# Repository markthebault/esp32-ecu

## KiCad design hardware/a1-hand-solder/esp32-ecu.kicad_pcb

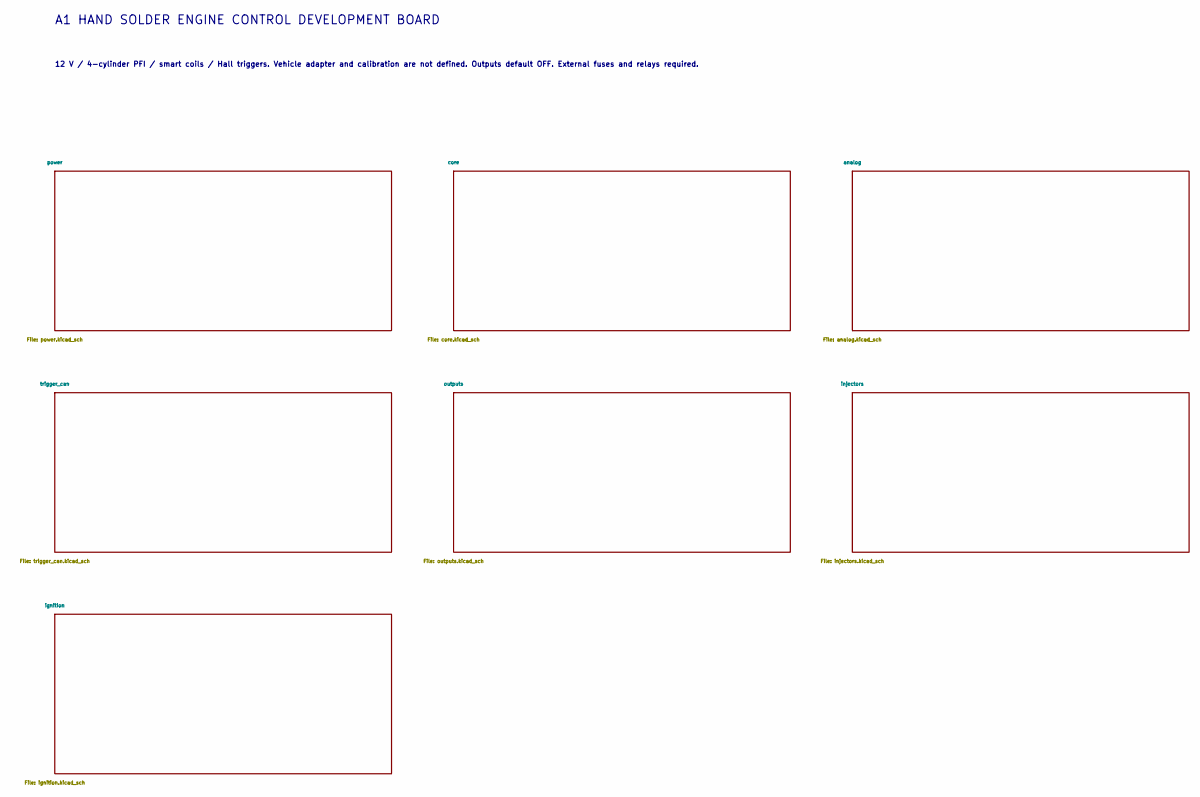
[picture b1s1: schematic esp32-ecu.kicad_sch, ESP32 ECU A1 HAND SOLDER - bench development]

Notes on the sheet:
A1 HAND SOLDER ENGINE CONTROL DEVELOPMENT BOARD
12 V / 4-cylinder PFI / smart coils / Hall triggers. Vehicle adapter and calibration are not defined. Outputs default OFF. External fuses and relays required.

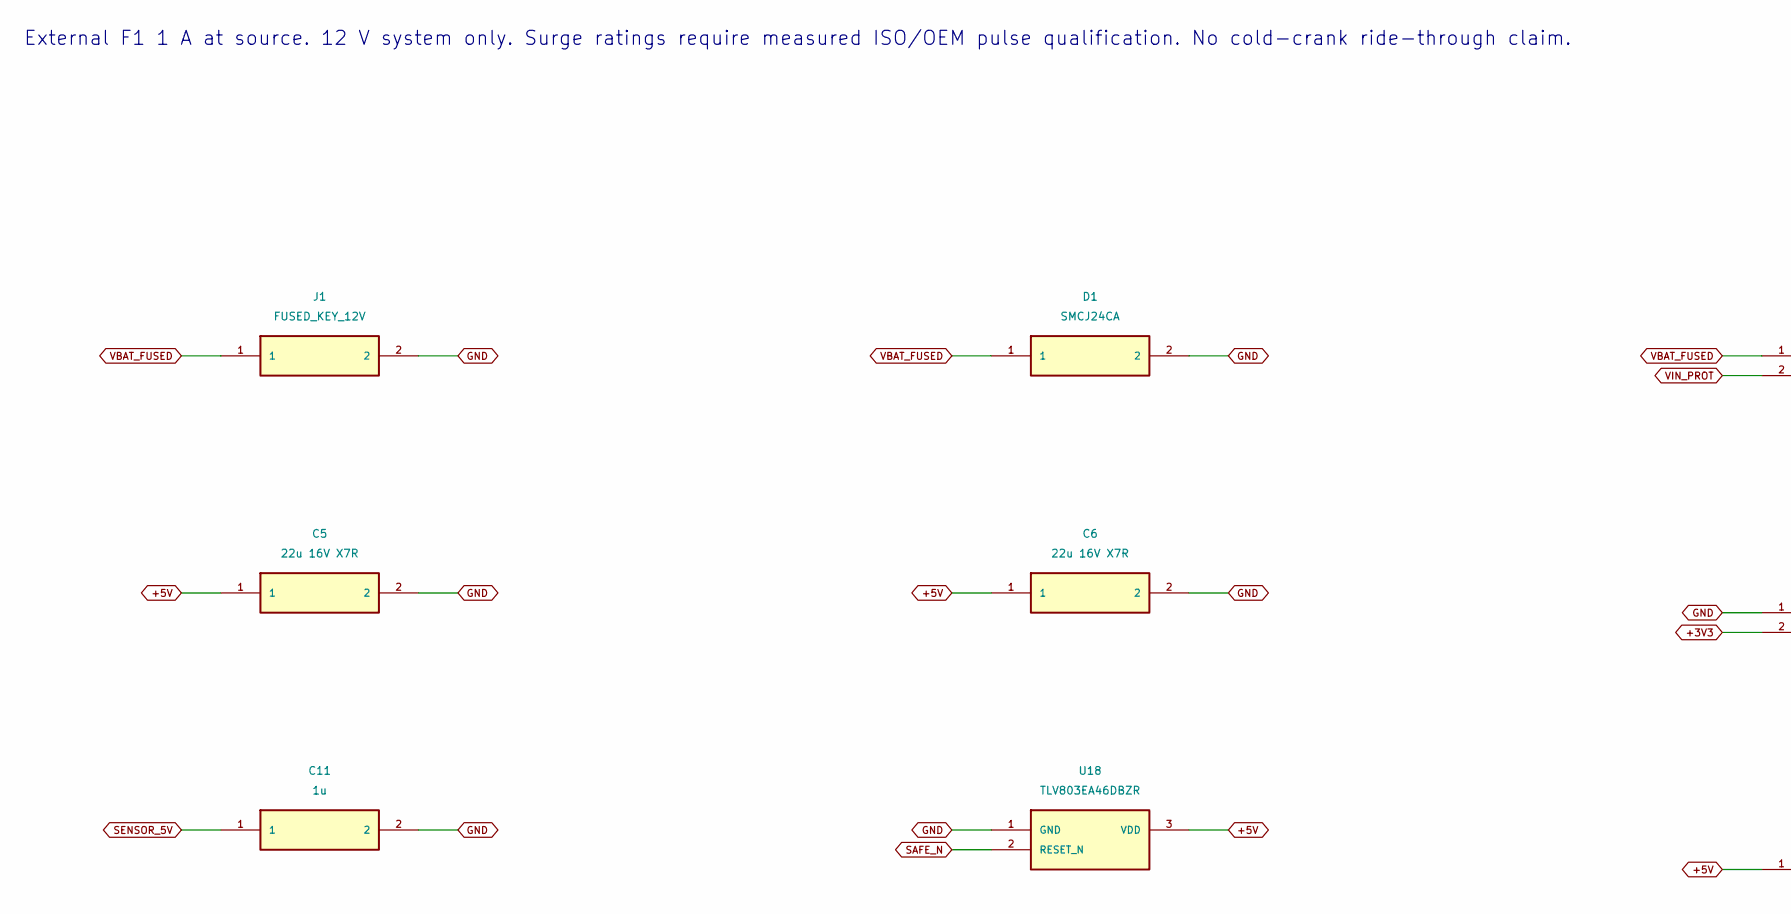
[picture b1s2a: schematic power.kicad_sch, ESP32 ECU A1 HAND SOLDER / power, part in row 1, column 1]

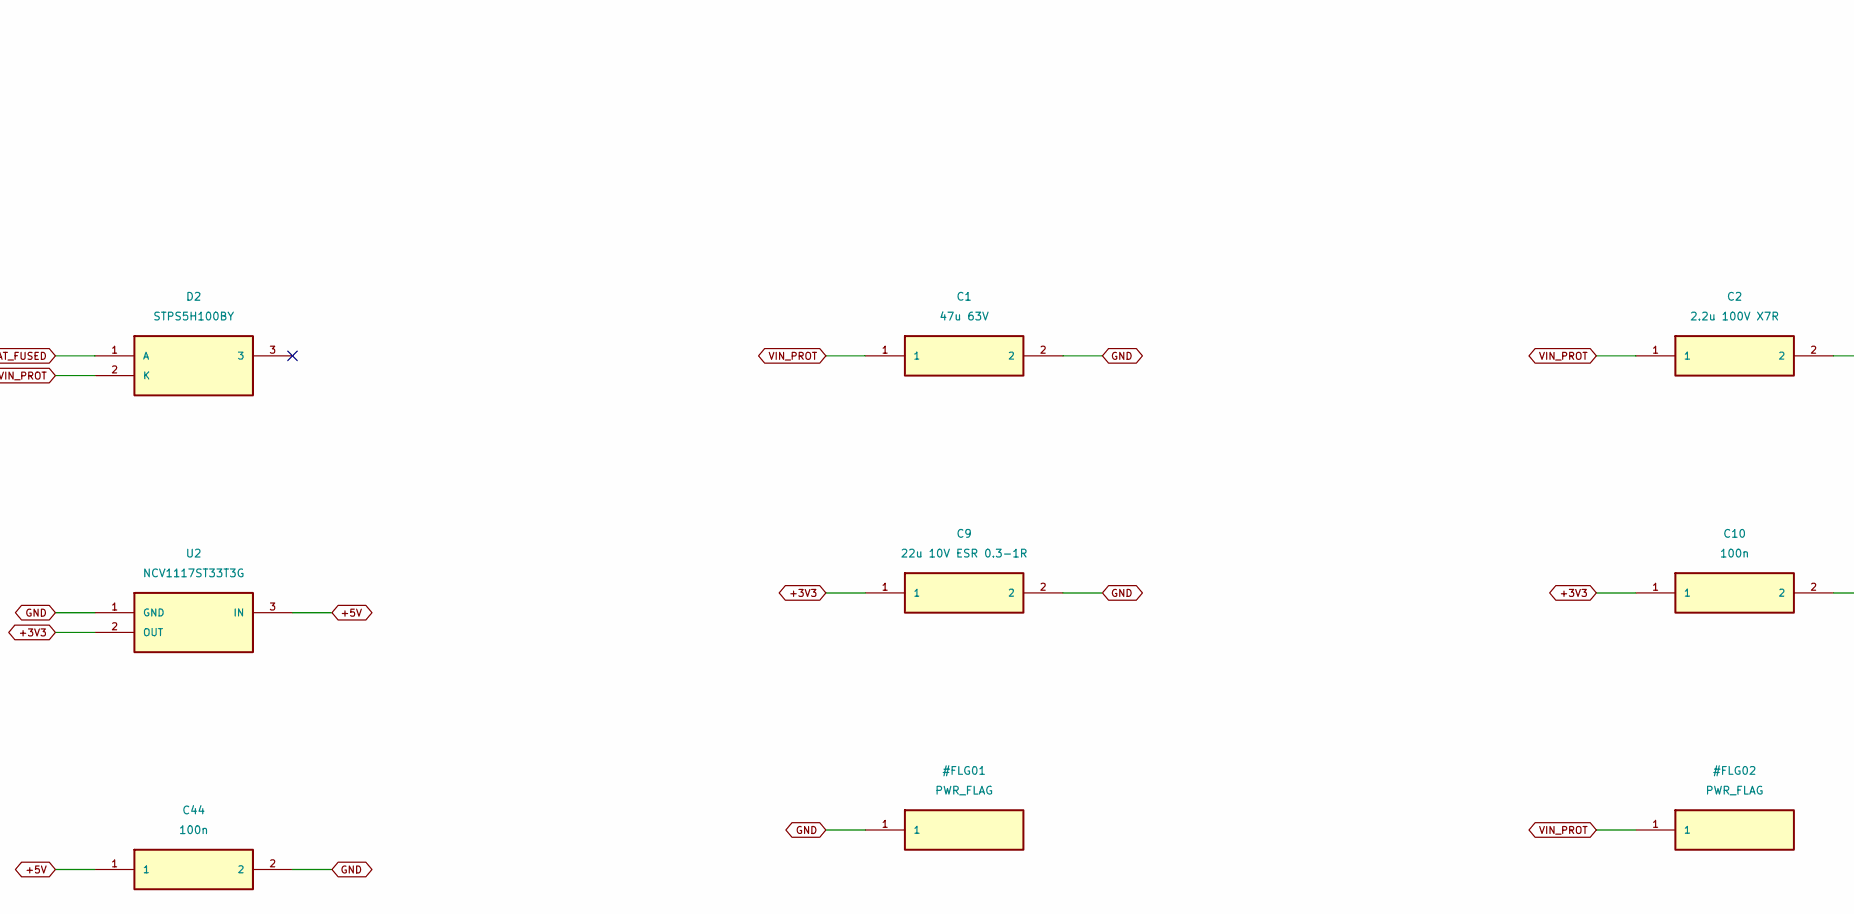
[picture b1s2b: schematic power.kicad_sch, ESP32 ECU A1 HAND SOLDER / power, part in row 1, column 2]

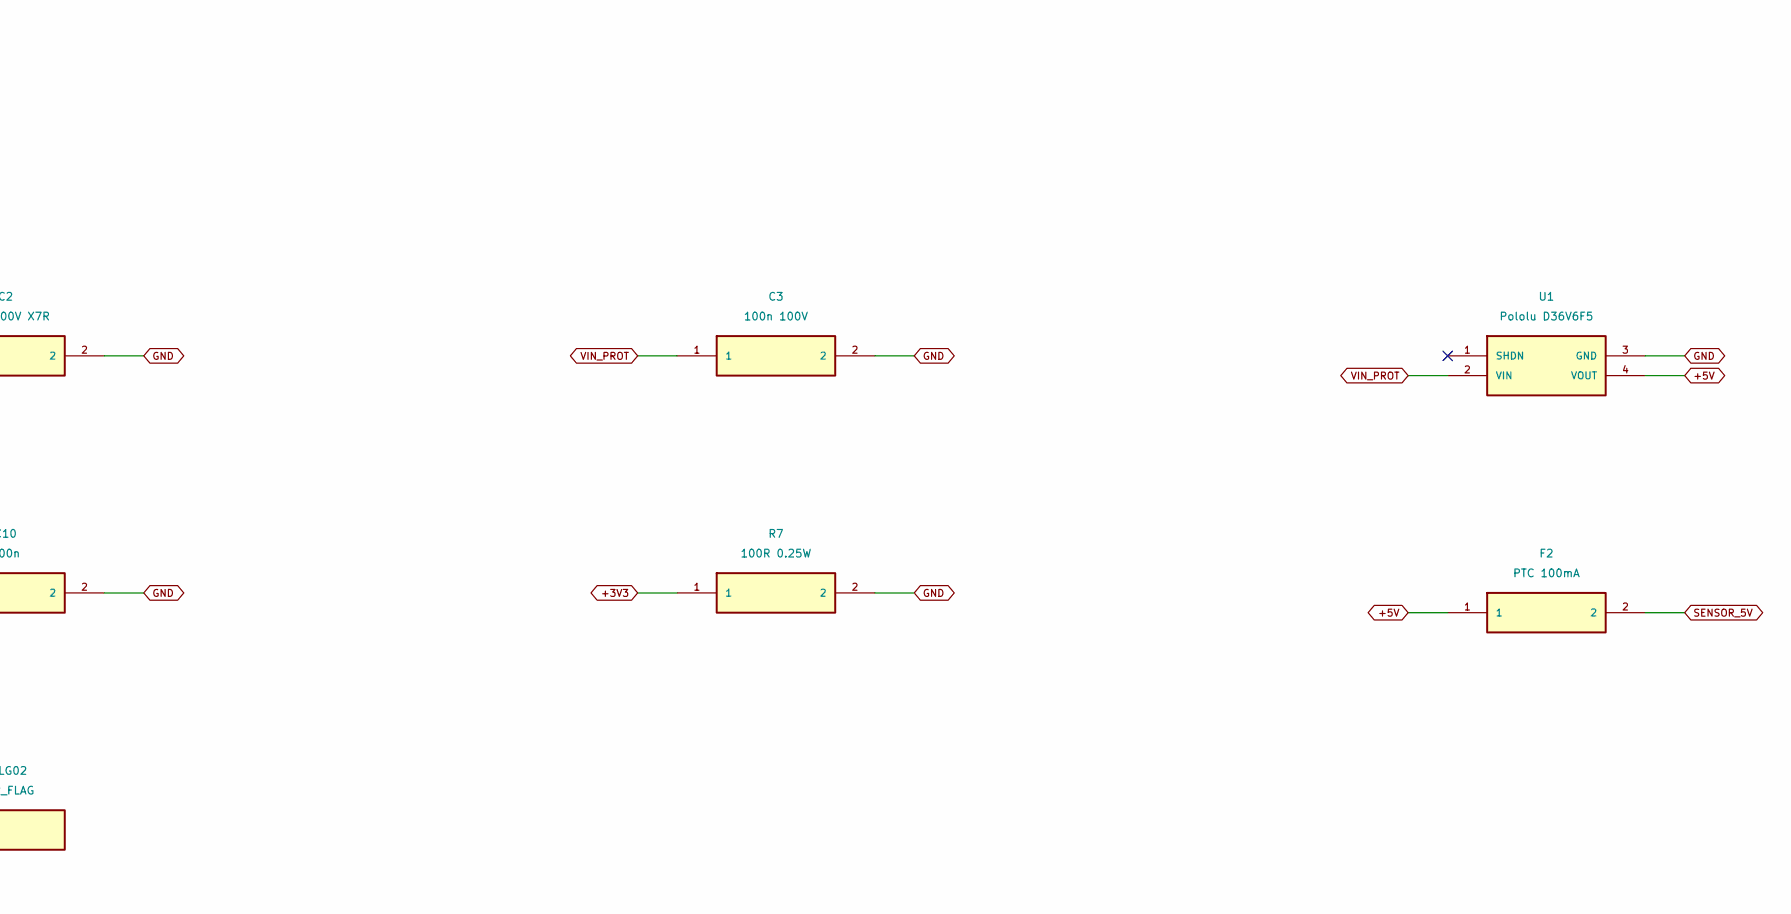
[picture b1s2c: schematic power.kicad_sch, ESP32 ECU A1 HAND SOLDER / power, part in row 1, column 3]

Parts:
C1: 47u 63V; CP_Elec_8x10
C2: 2.2u 100V X7R; C_1206_3216Metric_Pad1.33x1.80mm_HandSolder
C3: 100n 100V; C_1206_3216Metric_Pad1.33x1.80mm_HandSolder
C5, C6: 22u 16V X7R; C_1206_3216Metric_Pad1.33x1.80mm_HandSolder
C9: 22u 10V ESR 0.3-1R; CP_Elec_6.3x5.8
C10, C44: 100n; C_1206_3216Metric_Pad1.33x1.80mm_HandSolder
C11: 1u; C_1206_3216Metric_Pad1.33x1.80mm_HandSolder
D1: SMCJ24CA; D_SMC; MPN SMCJ24CA-E3/57T
D2: STPS5H100BY; TO-252-2; MPN STPS5H100BY
F2: PTC 100mA; Fuse_1812_4532Metric; MPN MF-MSMF010-2
J1: FUSED_KEY_12V; JST_VH_B2P-VH_1x02_P3.96mm_Vertical; MPN B2P-VH(LF)(SN)
R7: 100R 0.25W; R_1206_3216Metric_Pad1.30x1.75mm_HandSolder
U1: Pololu D36V6F5; Pololu_D36V6F5_vertical; MPN Pololu 3792
U2: NCV1117ST33T3G; SOT-223-3_TabPin2; MPN NCV1117ST33T3G
U18: TLV803EA46DBZR; SOT-23; MPN TLV803EA46DBZR

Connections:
+3V3: C9.1, C10.1, R7.1, U2.2 (OUT); also elsewhere on the board
+5V: C5.1, C6.1, C44.1, F2.1, U1.4 (VOUT), U2.3 (IN), U18.3 (VDD); also elsewhere on the board
GND: C1.2, C2.2, C3.2, C5.2, C6.2, C9.2, C10.2, C11.2, C44.2, D1.2, J1.2, R7.2, U1.3 (GND), U2.1 (GND), U18.1 (GND); also elsewhere on the board
SAFE_N: U18.2 (RESET_N); also elsewhere on the board
SENSOR_5V: C11.1, F2.2; also elsewhere on the board
VBAT_FUSED: D1.1, D2.1 (A), J1.1
VIN_PROT: C1.1, C2.1, C3.1, D2.2 (K), U1.2 (VIN); also elsewhere on the board

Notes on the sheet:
External F1 1 A at source. 12 V system only. Surge ratings require measured ISO/OEM pulse qualification. No cold-crank ride-through claim.

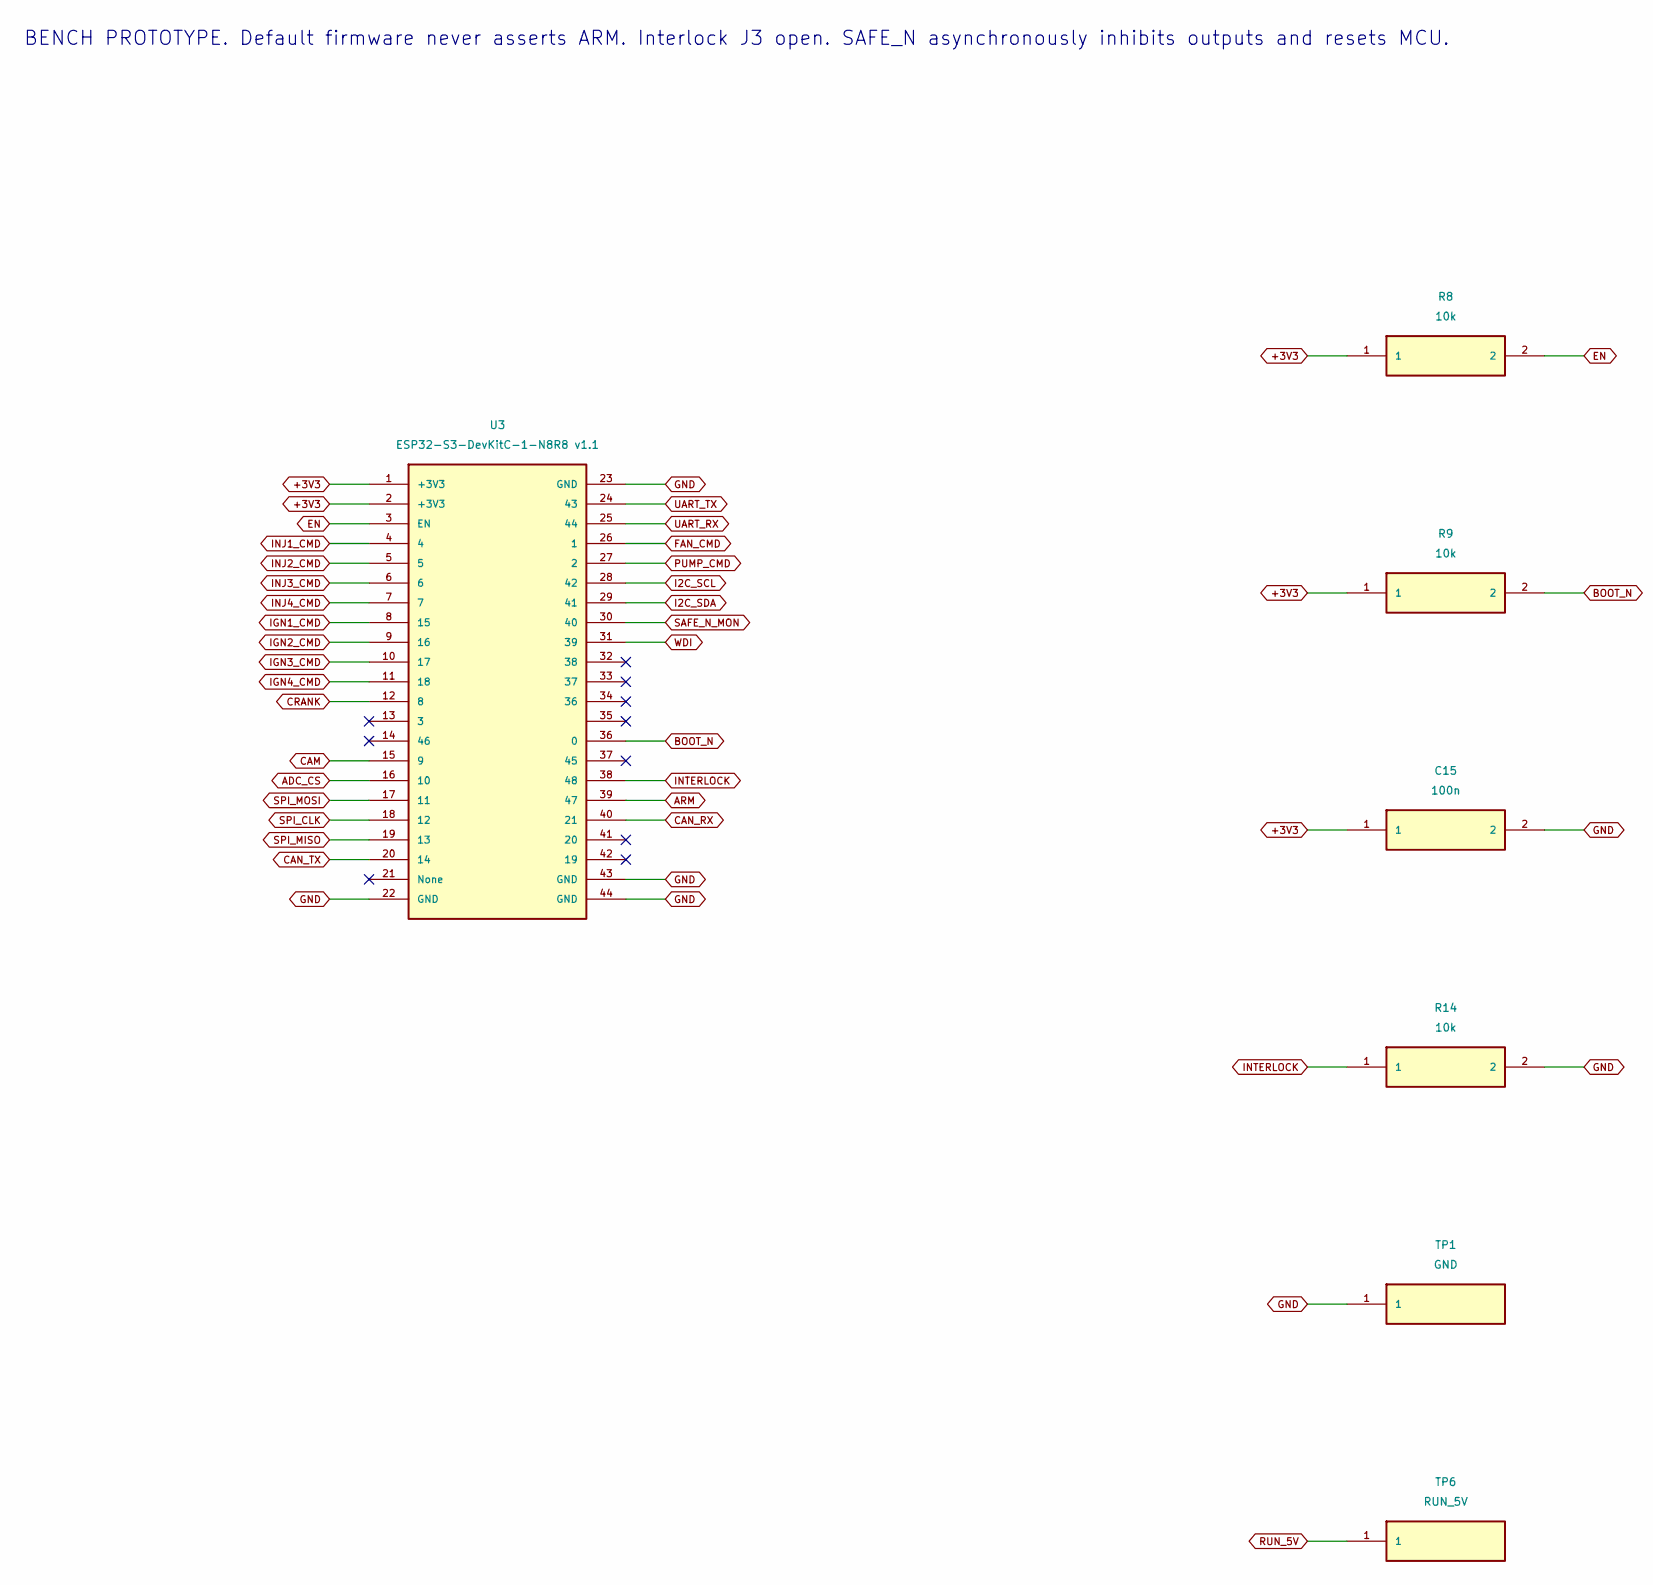
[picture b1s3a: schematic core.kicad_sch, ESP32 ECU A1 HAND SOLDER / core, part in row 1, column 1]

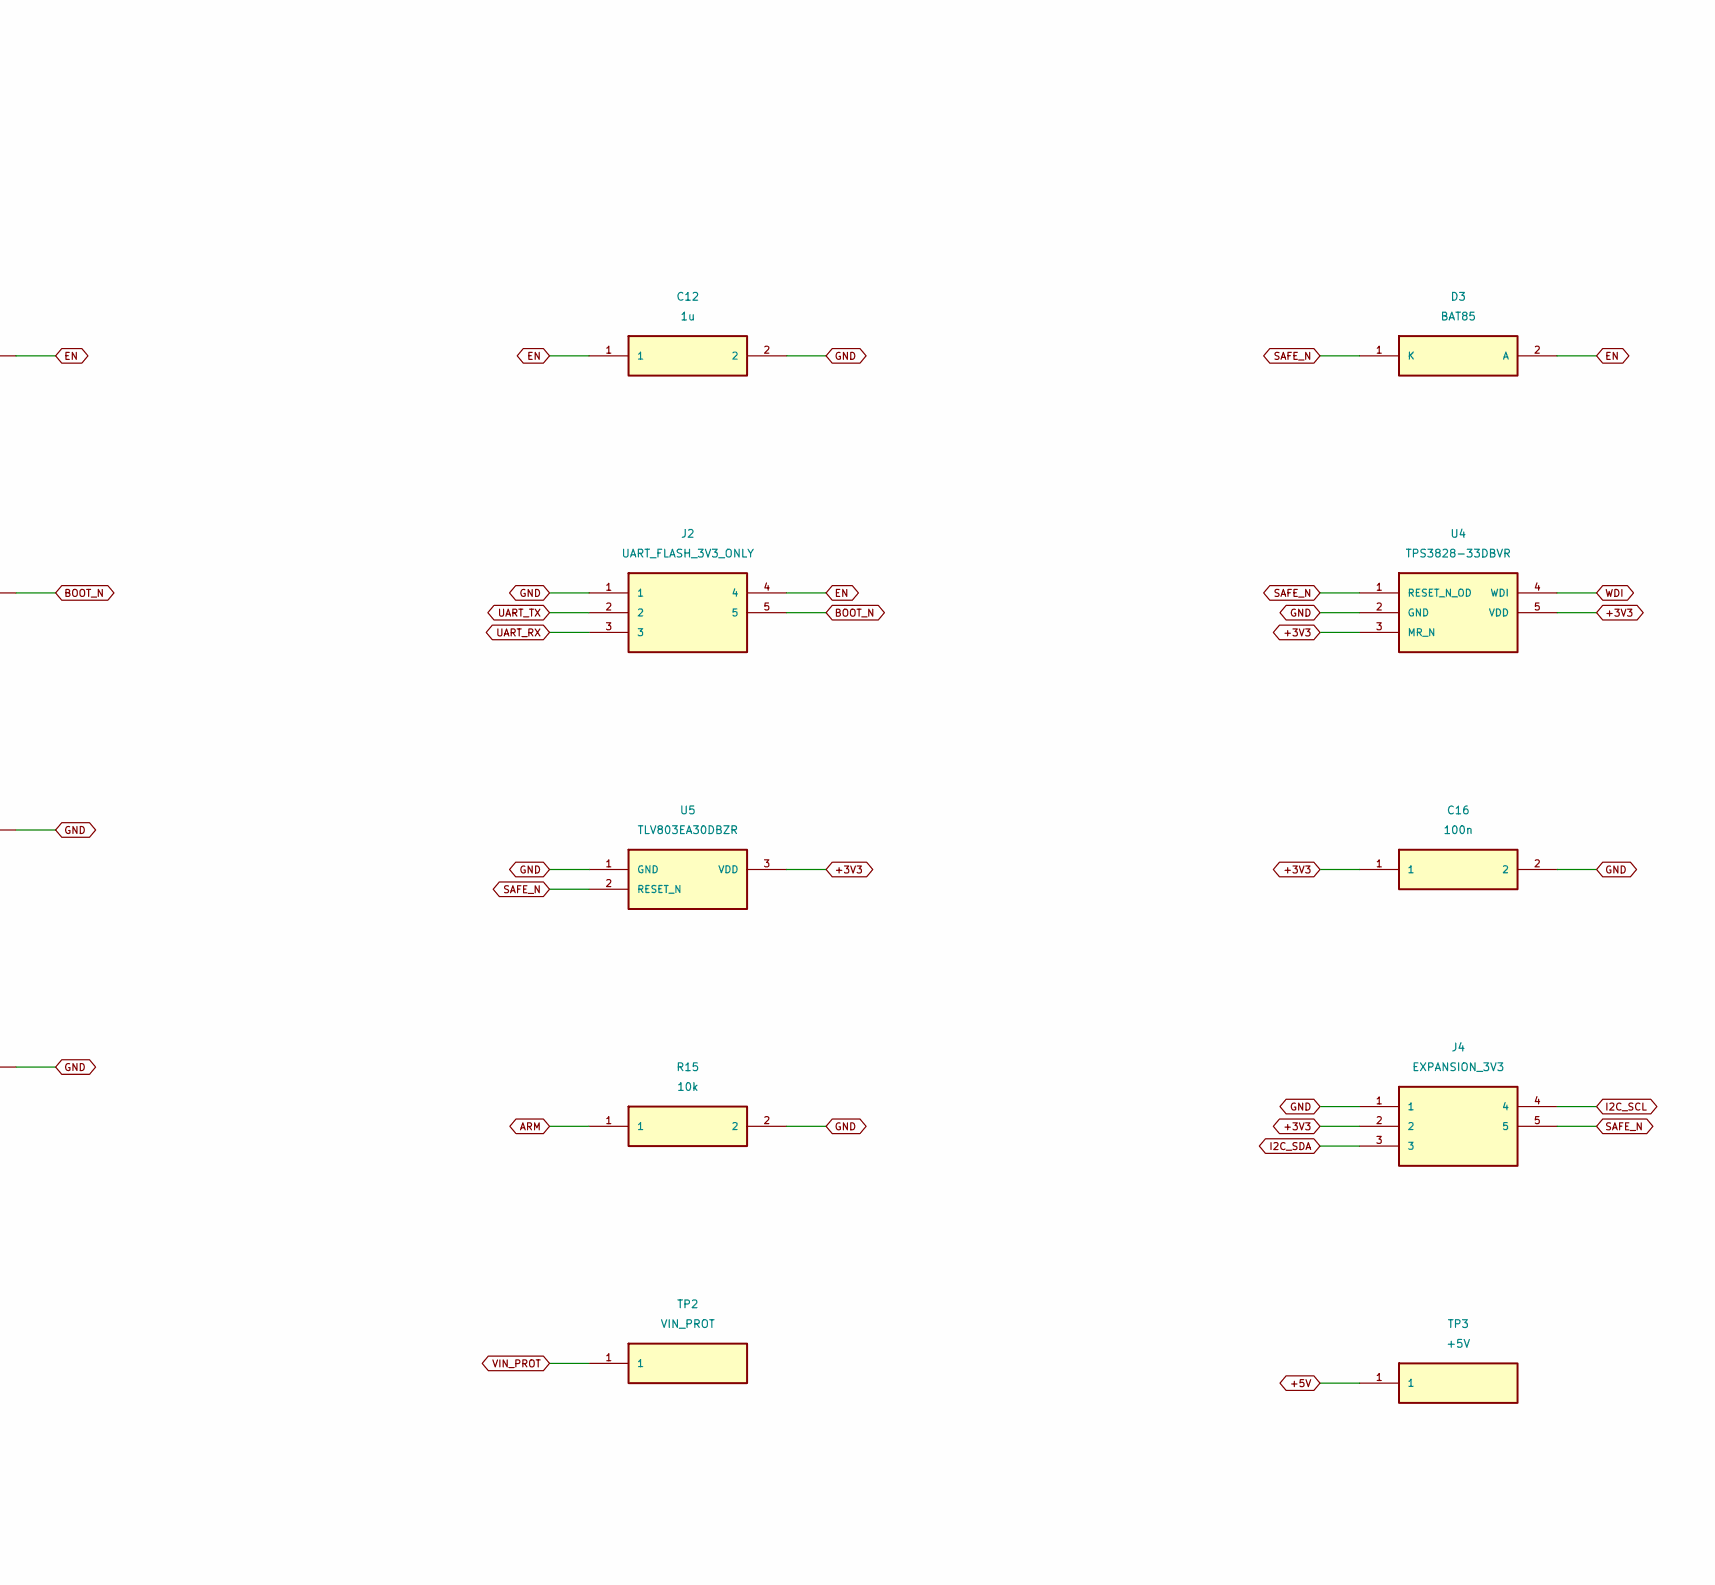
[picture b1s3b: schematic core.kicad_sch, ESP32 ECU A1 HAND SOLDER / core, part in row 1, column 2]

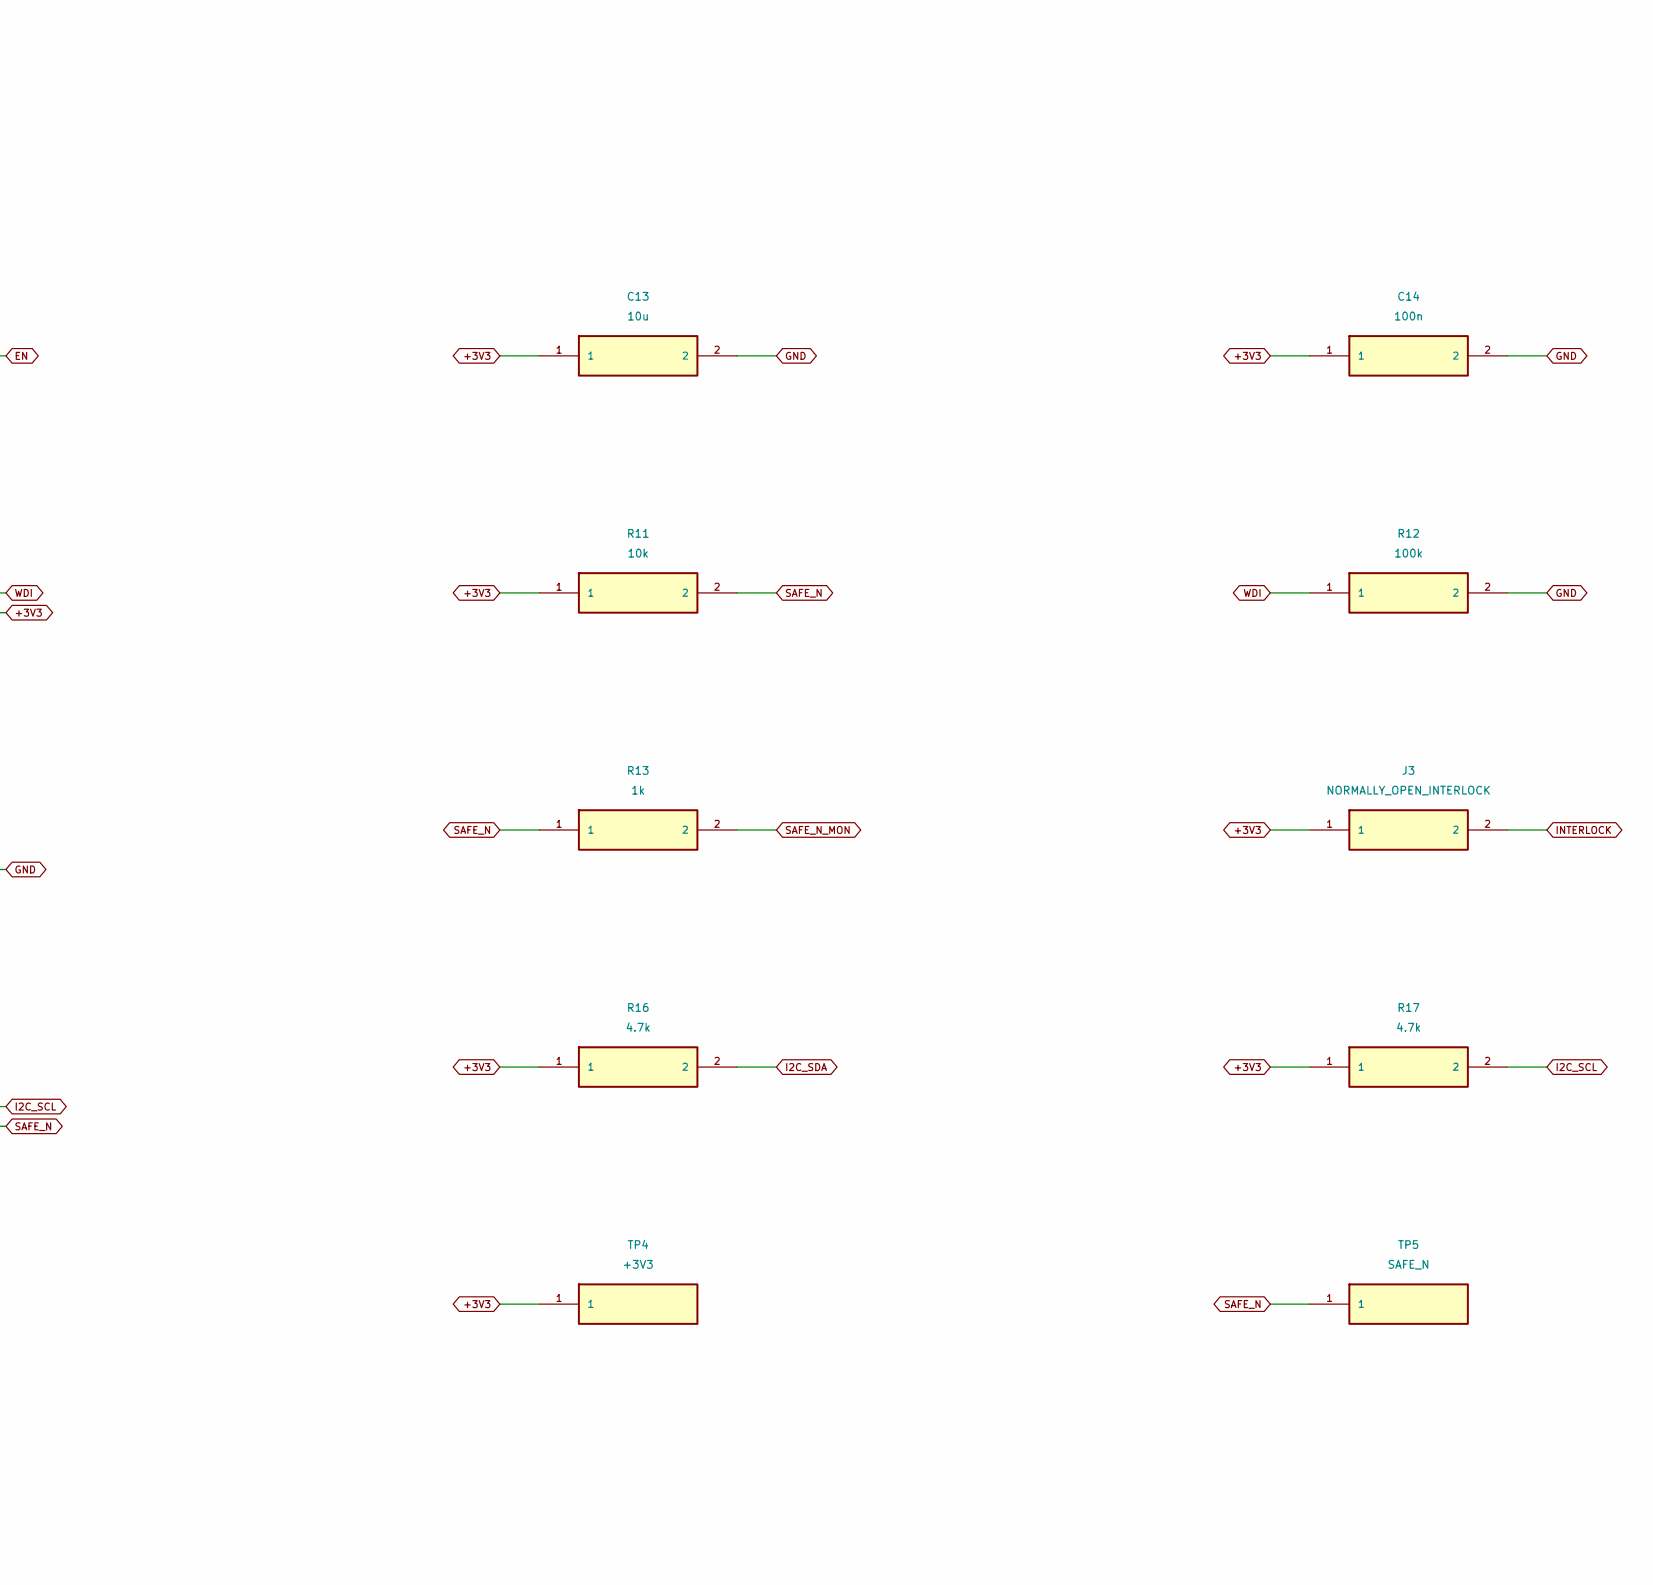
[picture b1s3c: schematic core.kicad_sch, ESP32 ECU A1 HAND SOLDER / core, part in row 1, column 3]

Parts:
C12: 1u; C_1206_3216Metric_Pad1.33x1.80mm_HandSolder
C13: 10u; C_1206_3216Metric_Pad1.33x1.80mm_HandSolder
C14, C15, C16: 100n; C_1206_3216Metric_Pad1.33x1.80mm_HandSolder
D3: BAT85; D_DO-35_SOD27_P3.81mm_Vertical_AnodeUp; MPN BAT85,113
J2: UART_FLASH_3V3_ONLY; PinHeader_1x05_P2.54mm_Vertical
J3: NORMALLY_OPEN_INTERLOCK; PinHeader_1x02_P2.54mm_Vertical
J4: EXPANSION_3V3; PinHeader_1x05_P2.54mm_Vertical
R8, R9, R11, R14, R15: 10k; R_1206_3216Metric_Pad1.30x1.75mm_HandSolder
R12: 100k; R_1206_3216Metric_Pad1.30x1.75mm_HandSolder
R13: 1k; R_1206_3216Metric_Pad1.30x1.75mm_HandSolder
R16, R17: 4.7k; R_1206_3216Metric_Pad1.30x1.75mm_HandSolder
TP1: GND; TestPoint_Pad_D2.0mm
TP2: VIN_PROT; TestPoint_Pad_D2.0mm
TP3: +5V; TestPoint_Pad_D2.0mm
TP4: +3V3; TestPoint_Pad_D2.0mm
TP5: SAFE_N; TestPoint_Pad_D2.0mm
TP6: RUN_5V; TestPoint_Pad_D2.0mm
U3: ESP32-S3-DevKitC-1-N8R8 v1.1; ESP32_S3_DevKitC_1_socket; MPN ESP32-S3-DevKitC-1-N8R8
U4: TPS3828-33DBVR; SOT-23-5; MPN TPS3828-33DBVR
U5: TLV803EA30DBZR; SOT-23; MPN TLV803EA30DBZR

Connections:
+3V3: C13.1, C14.1, C15.1, C16.1, J3.1, J4.2, R8.1, R9.1, R11.1, R16.1, R17.1, TP4.1, U3.1 (+3V3), U3.2 (+3V3), U4.3 (MR_N), U4.5 (VDD), U5.3 (VDD); also elsewhere on the board
+5V: TP3.1; also elsewhere on the board
ADC_CS: U3.16 (10); also elsewhere on the board
ARM: R15.1, U3.39 (47); also elsewhere on the board
BOOT_N: J2.5, R9.2, U3.36 (0)
CAM: U3.15 (9); also elsewhere on the board
CAN_RX: U3.40 (21); also elsewhere on the board
CAN_TX: U3.20 (14); also elsewhere on the board
CRANK: U3.12 (8); also elsewhere on the board
EN: C12.1, D3.2 (A), J2.4, R8.2, U3.3 (EN)
FAN_CMD: U3.26 (1); also elsewhere on the board
GND: C12.2, C13.2, C14.2, C15.2, C16.2, J2.1, J4.1, R12.2, R14.2, R15.2, TP1.1, U3.22 (GND), U3.23 (GND), U3.43 (GND), U3.44 (GND), U4.2 (GND), U5.1 (GND); also elsewhere on the board
I2C_SCL: J4.4, R17.2, U3.28 (42)
I2C_SDA: J4.3, R16.2, U3.29 (41)
IGN1_CMD: U3.8 (15); also elsewhere on the board
IGN2_CMD: U3.9 (16); also elsewhere on the board
IGN3_CMD: U3.10 (17); also elsewhere on the board
IGN4_CMD: U3.11 (18); also elsewhere on the board
INJ1_CMD: U3.4; also elsewhere on the board
INJ2_CMD: U3.5; also elsewhere on the board
INJ3_CMD: U3.6; also elsewhere on the board
INJ4_CMD: U3.7; also elsewhere on the board
INTERLOCK: J3.2, R14.1, U3.38 (48); also elsewhere on the board
PUMP_CMD: U3.27 (2); also elsewhere on the board
RUN_5V: TP6.1; also elsewhere on the board
SAFE_N: D3.1 (K), J4.5, R11.2, R13.1, TP5.1, U4.1 (RESET_N_OD), U5.2 (RESET_N); also elsewhere on the board
SAFE_N_MON: R13.2, U3.30 (40)
SPI_CLK: U3.18 (12); also elsewhere on the board
SPI_MISO: U3.19 (13); also elsewhere on the board
SPI_MOSI: U3.17 (11); also elsewhere on the board
UART_RX: J2.3, U3.25 (44)
UART_TX: J2.2, U3.24 (43)
VIN_PROT: TP2.1; also elsewhere on the board
WDI: R12.1, U3.31 (39), U4.4 (WDI)

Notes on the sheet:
BENCH PROTOTYPE. Default firmware never asserts ARM. Interlock J3 open. SAFE_N asynchronously inhibits outputs and resets MCU.
